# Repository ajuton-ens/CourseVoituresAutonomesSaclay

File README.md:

# Course de Voitures Autonomes Paris-Saclay CoVAPSy
Ce dépôt regroupe les documents et ressources liées à la course de voitures autonomes 1/10ème de Paris Saclay : https://ajuton-ens.github.io/CourseVoituresAutonomesSaclay/

Il est possible de s'inscrire ou d'obtenir plus d'informations en envoyant un mail à : anthony.juton@ens-paris-saclay.fr 

Le dossier _Simulator_ propose un simulateur Webots R2023b avec une voiture TT-02 équipée d'un lidar.
L'Efrei a aussi déposé un simulateur Webots.

Les cartes électroniques (pdf et fichiers Eagle) et les pièces mécaniques (fichiers step) de la voiture type sont dans le dossier _Hardware_.

---------------------------------------------
# Autonomous Car Race Paris-Saclay CoVAPSy

This repository contains documents and resources related to the 1/10th self-driving car race in Paris-Saclay: https://ajuton-ens.github.io/CourseVoituresAutonomesSaclay/

You can register or obtain more information by sending an email to: anthony.juton@ens-paris-saclay.fr

The folder _Simulator_ includes a Webots R2023b simulator with a TT-02 car equipped with a lidar.
Efrei has also submitted a Webots simulator.

The electronic boards (PDF and Eagle files) and mechanical parts (Step files) for the typical car are in the folder _Hardware_.

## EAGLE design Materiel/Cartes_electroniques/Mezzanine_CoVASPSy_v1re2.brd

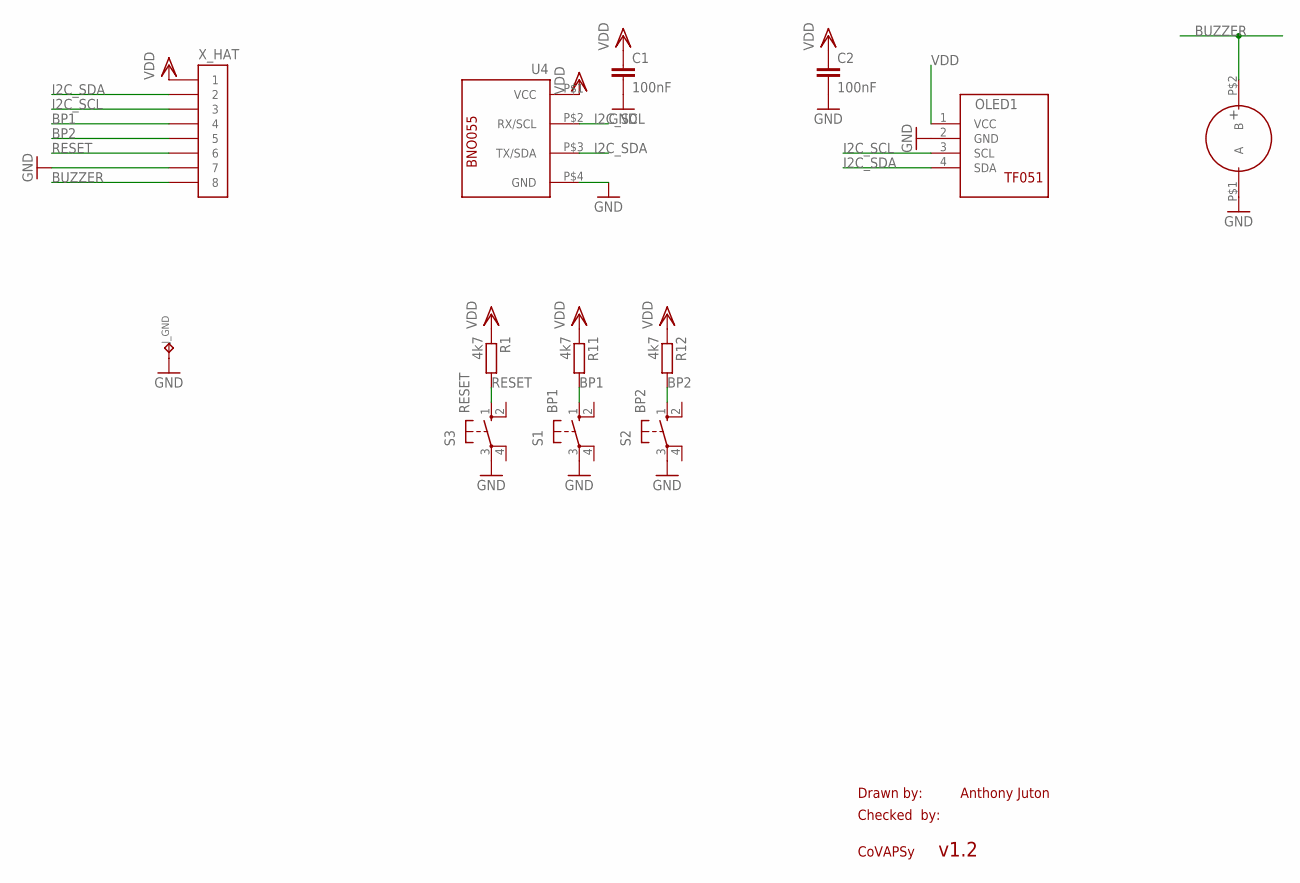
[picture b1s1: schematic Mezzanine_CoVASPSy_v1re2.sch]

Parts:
BUZZER: BUZZER_SMA13_P75; BUZZER_SMA_13_P75
C1, C2: 100nF; C1206K
J_GND: COSSE_POIGN; COSSE_POIGNARD
OLED1: ECRAN_OLED_TF051
R1, R11, R12: 4k7; M1206
S1: BP1; B3F-10XX
S2: BP2; B3F-10XX
S3: RESET; B3F-10XX
U4: MODULE_BNO055
X_HAT: MOLEX_8_COUDE

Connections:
BP1: R11.2, S1.1 (S), X_HAT.P$4 (4)
BP2: R12.2, S2.1 (S), X_HAT.P$5 (5)
BUZZER: BUZZER.P$2 (B), X_HAT.P$8 (8)
GND: BUZZER.P$1 (A), C1.2, C2.2, J_GND.P$1, OLED1.2 (GND), S1.3, S2.3, S3.3, U4.P$4 (GND), X_HAT.P$7 (7)
I2C_SCL: OLED1.3 (SCL), U4.P$2 (RX/SCL), X_HAT.P$3 (3)
I2C_SDA: OLED1.4 (SDA), U4.P$3 (TX/SDA), X_HAT.P$2 (2)
RESET: R1.2, S3.1 (S), X_HAT.P$6 (6)
VDD: C1.1, C2.1, OLED1.1 (VCC), R1.1, R11.1, R12.1, U4.P$1 (VCC), X_HAT.P$1 (1)

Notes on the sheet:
Drawn by:
Checked by:
CoVAPSy
Anthony Juton
v1.2

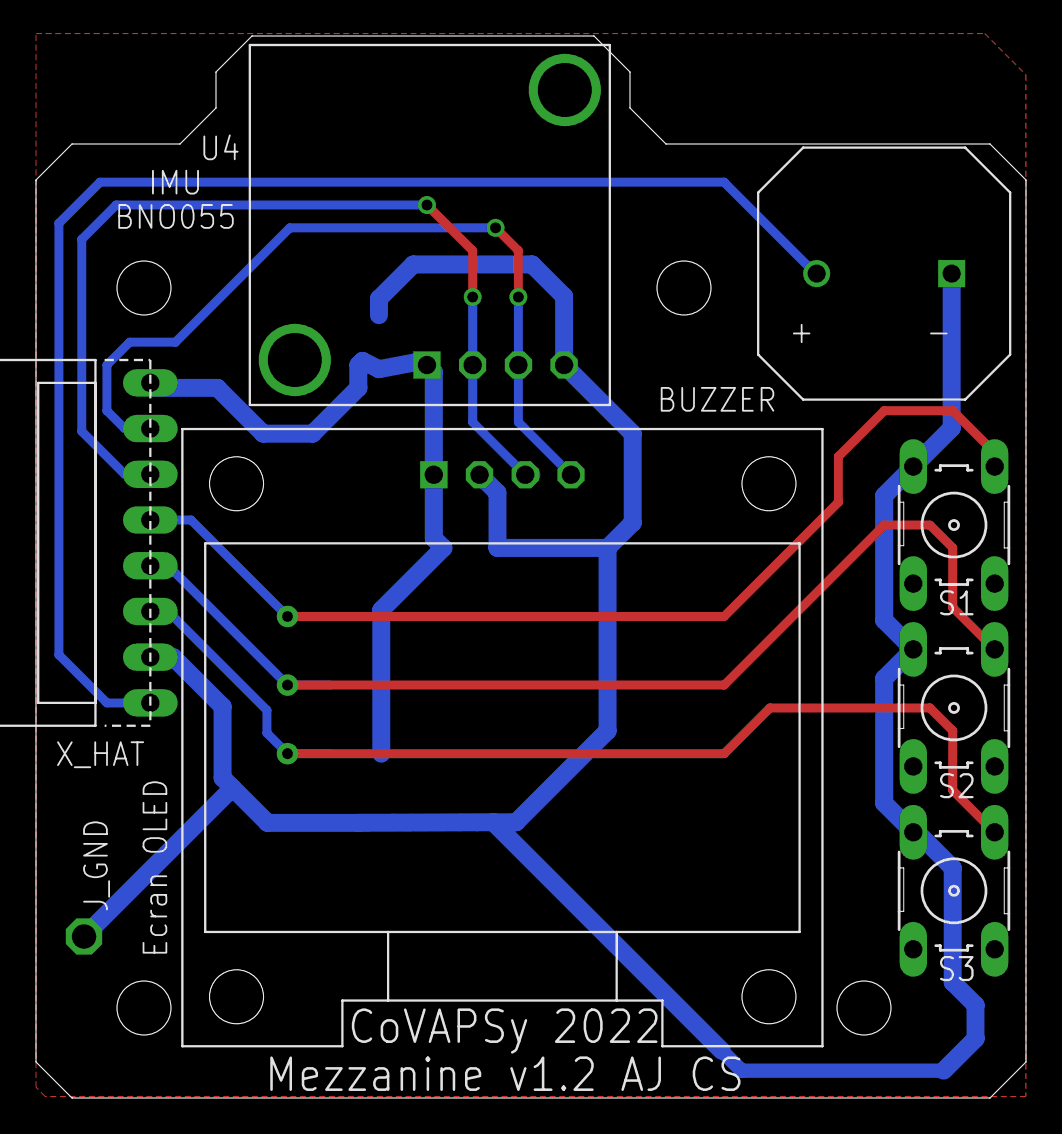
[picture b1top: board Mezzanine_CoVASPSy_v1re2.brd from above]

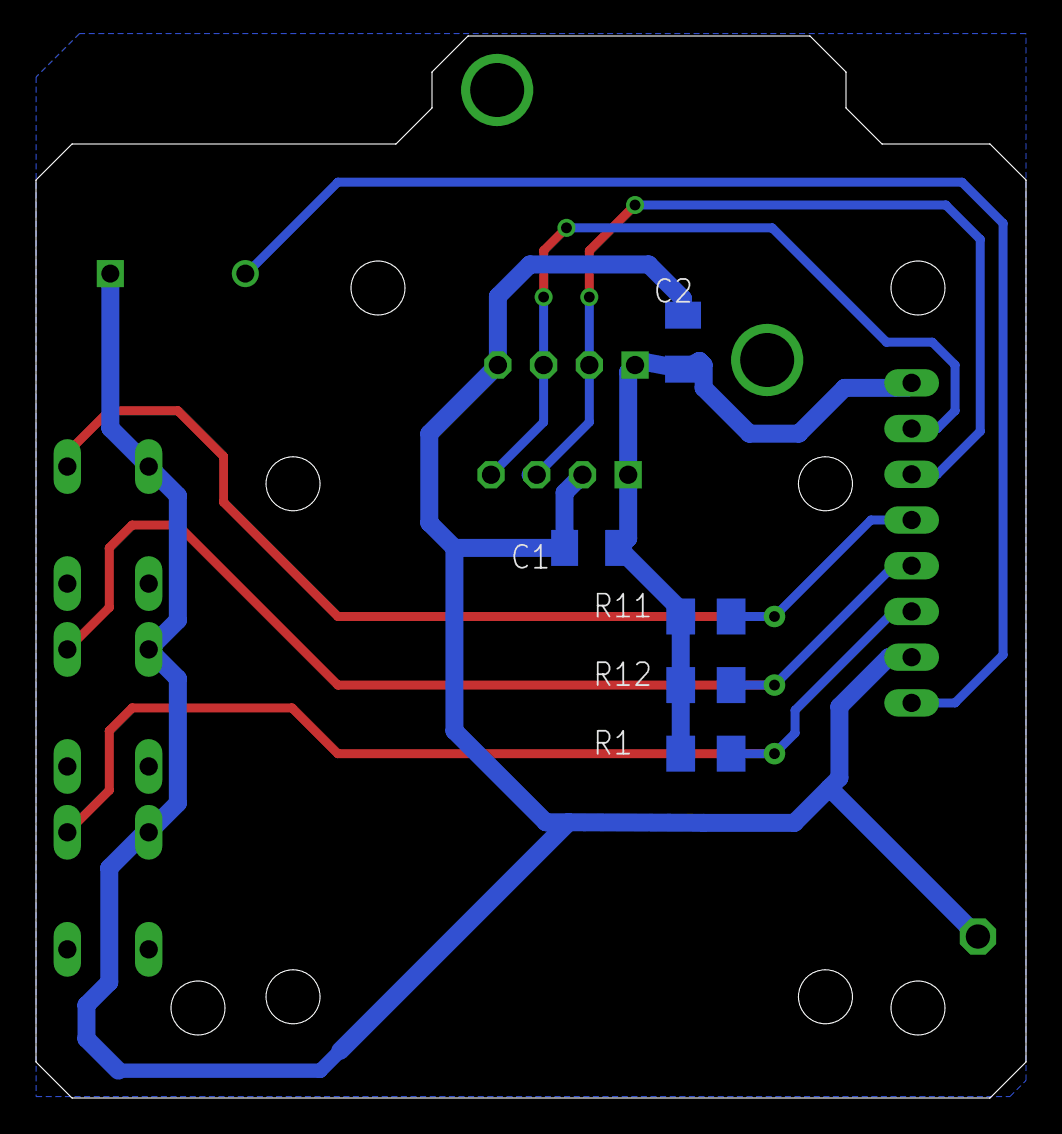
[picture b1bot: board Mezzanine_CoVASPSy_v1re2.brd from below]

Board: 2 copper layers, 55.0 x 59.0 mm, 13 parts (5 on the bottom side), 8 nets.

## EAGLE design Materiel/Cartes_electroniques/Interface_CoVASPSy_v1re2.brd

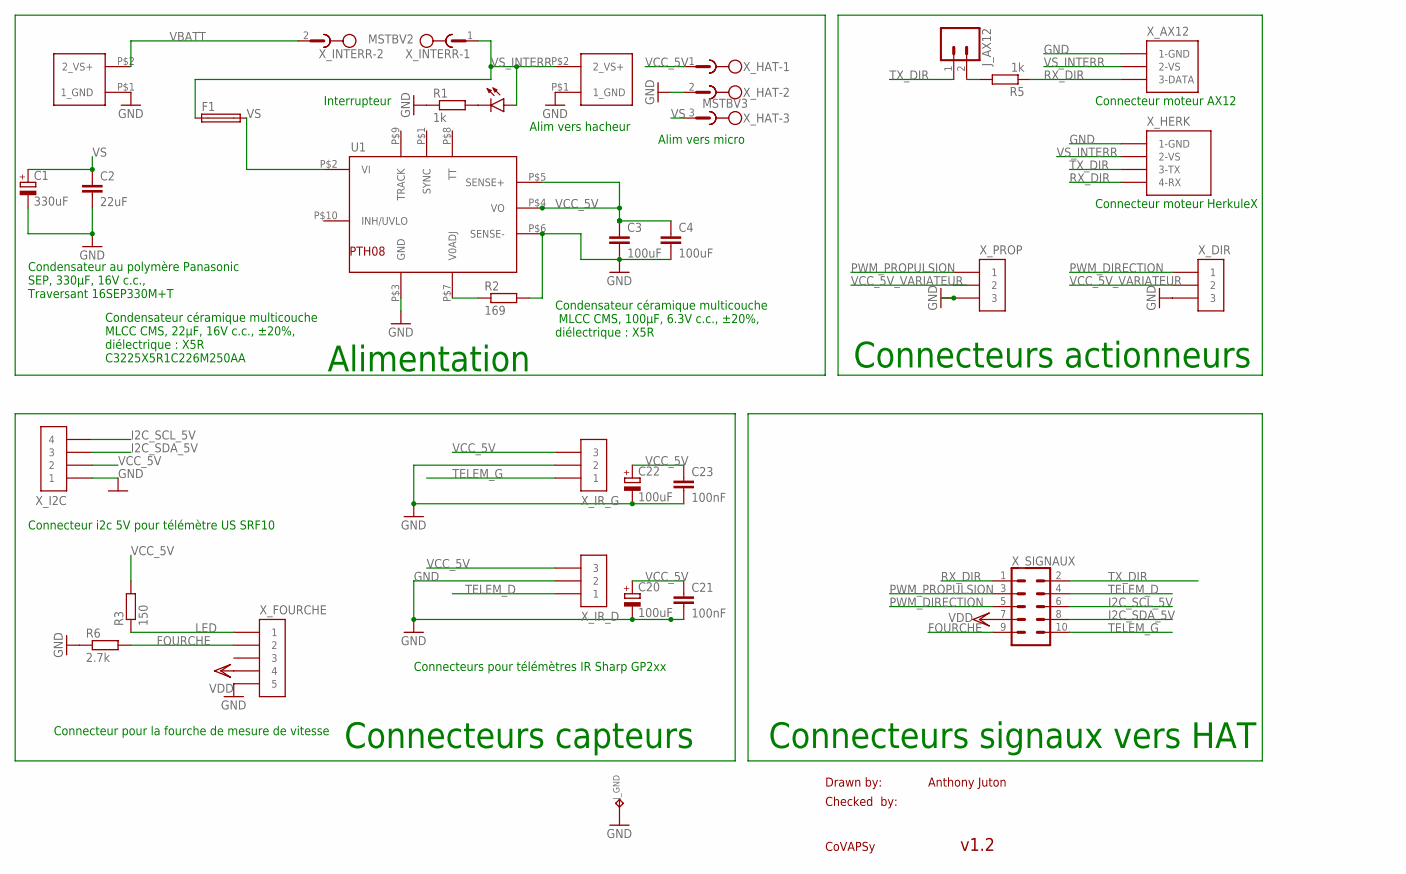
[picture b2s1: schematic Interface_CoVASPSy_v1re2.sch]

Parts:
C1: 330uF; E3,5-10
C2: 22uF; C1210
C3, C4: 100uF; C1206K
C20, C22: 100uF; A/3216-18W
C21, C23: 100nF; C1206
F1: SH22,5
J_AX12: CONN_02; 1X02
J_GND: COSSE_POIGN; COSSE_POIGNARD
LED1: LEDSML1206; SML1206
R1, R5: 1k; M1206
R2: 169; R0805
R3: 150; M1206
R6: 2.7k; M1206
U1: CONV_TI_PTH08; CONV_TI_PTH8
X_AX12: MOLEX_AX12
X_BATT: CONN_ALIM_TROU
X_DIR: CAVALIER_3
X_FOURCHE: MOLEX_5_DROIT
X_HACH: CONN_ALIM_TROU
X_HAT: MSTBV3
X_HERK: TE_HERKULEX
X_I2C: MOLEX_4_DROIT
X_INTERR: MSTBV2
X_IR_D: JST_3
X_IR_G: JST_3
X_PROP: CAVALIER_3
X_SIGNAUX: CONN_05X2SHD; 2X5-SHROUDED

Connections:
FOURCHE: R6.2, X_FOURCHE.P$2 (2), X_SIGNAUX.9
GND: C1.-, C2.2, C3.2, C4.2, C20.-, C21.2, C22.-, C23.2, J_GND.P$1, R1.1, R2.2, R6.1, U1.P$3 (GND), U1.P$6 (SENSE-), X_AX12.P$1 (1-GND), X_BATT.P$1 (1_GND), X_DIR.P$3 (3), X_FOURCHE.P$5 (5), X_HACH.P$1 (1_GND), X_HAT.2, X_HERK.P$1 (1-GND), X_I2C.P$1 (1), X_IR_D.P$2 (2), X_IR_G.P$2 (2), X_PROP.P$3 (3)
I2C_SCL_5V: X_I2C.P$4 (4), X_SIGNAUX.6
I2C_SDA_5V: X_I2C.P$3 (3), X_SIGNAUX.8
LED: R3.1, X_FOURCHE.P$1 (1)
unnamed: LED1.C, R1.2
unnamed: J_AX12.2, R5.2
unnamed: R2.1, U1.P$7 (V0ADJ)
PWM_DIRECTION: X_DIR.P$1 (1), X_SIGNAUX.5
PWM_PROPULSION: X_PROP.P$1 (1), X_SIGNAUX.3
RX_DIR: R5.1, X_AX12.P$3 (3-DATA), X_HERK.P$4 (4-RX), X_SIGNAUX.1
TELEM_D: X_IR_D.P$1 (1), X_SIGNAUX.4
TELEM_G: X_IR_G.P$1 (1), X_SIGNAUX.10
TX_DIR: J_AX12.1, X_HERK.P$3 (3-TX), X_SIGNAUX.2
VBATT: X_BATT.P$2 (2_VS+), X_INTERR.2
VCC_5V: C3.1, C4.1, C20.+, C21.1, C22.+, C23.1, R3.2, U1.P$4 (VO), U1.P$5 (SENSE+), X_HAT.1, X_I2C.P$2 (2), X_IR_D.P$3 (3), X_IR_G.P$3 (3)
VCC_5V_VARIATEUR: X_DIR.P$2 (2), X_PROP.P$2 (2)
VDD: X_FOURCHE.P$4 (4), X_SIGNAUX.7
VS: C1.+, C2.1, F1.2, U1.P$2 (VI), X_HAT.3
VS_INTERR: F1.1, LED1.A, X_AX12.P$2 (2-VS), X_HACH.P$2 (2_VS+), X_HERK.P$2 (2-VS), X_INTERR.1

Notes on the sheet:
Drawn by:
Checked by:
CoVAPSy
Anthony Juton
v1.2
Connecteur moteur AX12
Connecteur pour la fourche de mesure de vitesse
Connecteur moteur HerkuleX
Connecteurs actionneurs
Condensateur au polymère Panasonic SEP, 330μF, 16V c.c., Traversant 16SEP330M+T
Condensateur céramique multicouche MLCC CMS, 22μF, 16V c.c., ±20%, diélectrique : X5R C3225X5R1C226M250AA
Condensateur céramique multicouche MLCC CMS, 100μF, 6.3V c.c., ±20%, diélectrique : X5R
Alimentation
Alim vers hacheur
Interrupteur
Alim vers micro
Connecteurs capteurs
Connecteur i2c 5V pour télémètre US SRF10
Connecteurs pour télémètres IR Sharp GP2xx
Connecteurs signaux vers HAT

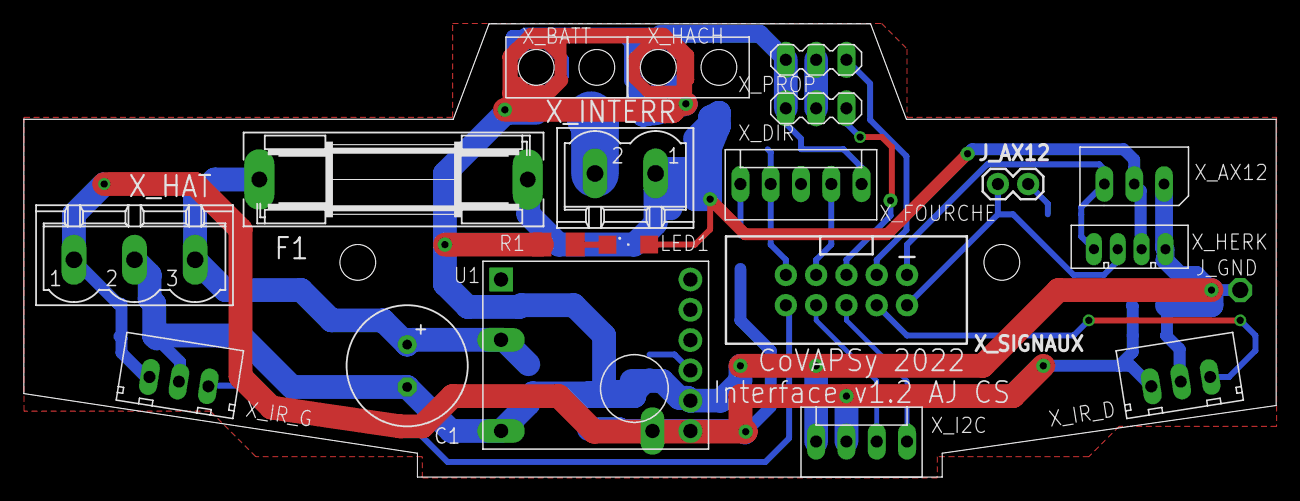
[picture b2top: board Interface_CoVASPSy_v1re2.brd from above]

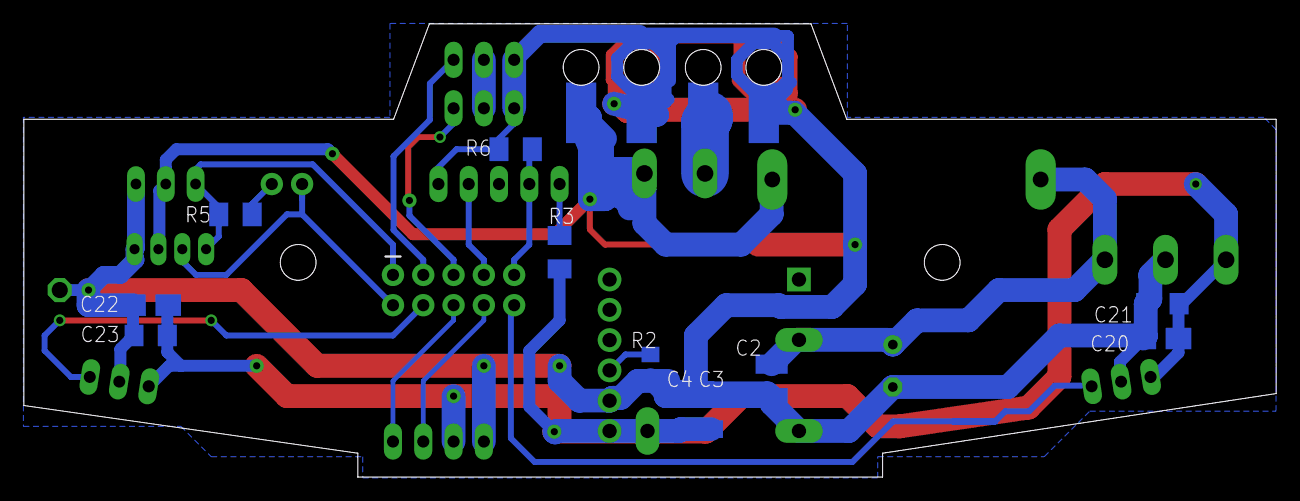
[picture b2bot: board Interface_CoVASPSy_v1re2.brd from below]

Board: 2 copper layers, 105.0 x 38.0 mm, 31 parts (11 on the bottom side), 20 nets.

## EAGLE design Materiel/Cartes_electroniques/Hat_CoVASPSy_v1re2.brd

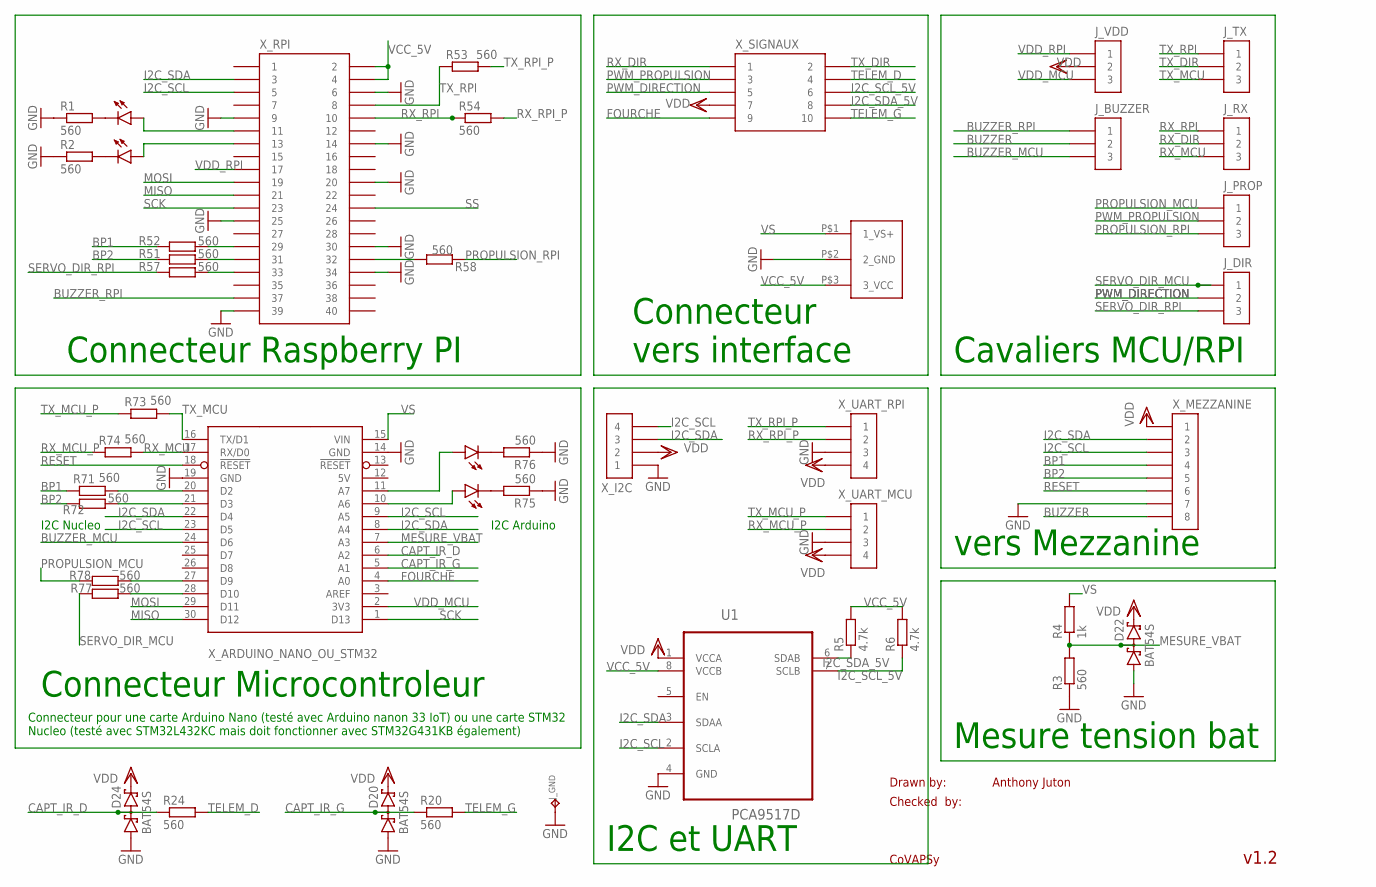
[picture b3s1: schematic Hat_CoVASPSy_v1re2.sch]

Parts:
D20, D22, D24: BAT54S; SOT23
J_BUZZER: CAVALIER_3
J_DIR: CAVALIER_3
J_GND: COSSE_POIGN; COSSE_POIGNARD
J_PROP: CAVALIER_3
J_RX: CAVALIER_3
J_TX: CAVALIER_3
J_VDD: CAVALIER_3
LED1, LED2, LED3, LED4: LEDSML1206; SML1206
R1, R2, R3, R20, R24, R51, R52, R53, R54, R57, R58, R71, R72, R73, R74, R75, R76, R77, R78: 560; M1206
R4: 1k; M1206
R5, R6: 4.7k; M1206
U1: PCA9517D; SOIC127P600X175-8N
X_ALIM: CONN_ALIM_3TROUS
X_ARDUINO_NANO_OU_STM32: ARDUINO_NANO_STM32_NUCLEO
X_I2C: MOLEX_4_DROIT
X_MEZZANINE: MOLEX_8_DROIT
X_RPI: HEADER_20X2
X_SIGNAUX: HEADER_5X2
X_UART_MCU: MOLEX_4_DROIT
X_UART_RPI: MOLEX_4_DROIT

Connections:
5V: X_ARDUINO_NANO_OU_STM32.12 (5V)
BP1: R52.1, R71.1, X_MEZZANINE.P$4 (4)
BP2: R51.1, R72.1, X_MEZZANINE.P$5 (5)
BUZZER: J_BUZZER.P$2 (2), X_MEZZANINE.P$8 (8)
BUZZER_MCU: J_BUZZER.P$3 (3), X_ARDUINO_NANO_OU_STM32.24 (D6)
BUZZER_RPI: J_BUZZER.P$1 (1), X_RPI.P$37 (37)
CAPT_IR_D: D24.3 (C1A2), R24.1, X_ARDUINO_NANO_OU_STM32.6 (A2)
CAPT_IR_G: D20.3 (C1A2), R20.1, X_ARDUINO_NANO_OU_STM32.5 (A1)
FOURCHE: X_ARDUINO_NANO_OU_STM32.4 (A0), X_SIGNAUX.P$9 (9)
GND: D20.1 (A1), D22.1 (A1), D24.1 (A1), J_GND.P$1, R1.1, R2.1, R3.1, R75.1, R76.1, U1.4 (GND), X_ALIM.P$2 (2_GND), X_ARDUINO_NANO_OU_STM32.14 (GND), X_ARDUINO_NANO_OU_STM32.19 (GND), X_I2C.P$1 (1), X_MEZZANINE.P$7 (7), X_RPI.P$6 (6), X_RPI.P$9 (9), X_RPI.P$14 (14), X_RPI.P$20 (20), X_RPI.P$25 (25), X_RPI.P$30 (30), X_RPI.P$34 (34), X_RPI.P$39 (39), X_UART_MCU.P$3 (3), X_UART_RPI.P$3 (3)
I2C_SCL: U1.2 (SCLA), X_ARDUINO_NANO_OU_STM32.9 (A5), X_ARDUINO_NANO_OU_STM32.23 (D5), X_I2C.P$4 (4), X_MEZZANINE.P$3 (3), X_RPI.P$5 (5)
I2C_SCL_5V: R6.1, U1.7 (SCLB), X_SIGNAUX.P$6 (6)
I2C_SDA: U1.3 (SDAA), X_ARDUINO_NANO_OU_STM32.8 (A4), X_ARDUINO_NANO_OU_STM32.22 (D4), X_I2C.P$3 (3), X_MEZZANINE.P$2 (2), X_RPI.P$3 (3)
I2C_SDA_5V: R5.1, U1.6 (SDAB), X_SIGNAUX.P$8 (8)
MESURE_VBAT: D22.3 (C1A2), R3.2, R4.1, X_ARDUINO_NANO_OU_STM32.7 (A3)
MISO: X_ARDUINO_NANO_OU_STM32.30 (D12), X_RPI.P$21 (21)
MOSI: X_ARDUINO_NANO_OU_STM32.29 (D11), X_RPI.P$19 (19)
unnamed: LED1.C, R1.2
unnamed: LED3.A, X_ARDUINO_NANO_OU_STM32.11 (A7)
unnamed: R71.2, X_ARDUINO_NANO_OU_STM32.20 (D2)
unnamed: R72.2, X_ARDUINO_NANO_OU_STM32.21 (D3)
unnamed: LED2.C, R2.2
unnamed: LED1.A, X_RPI.P$11 (11)
unnamed: R52.2, X_RPI.P$29 (29)
unnamed: R77.2, X_ARDUINO_NANO_OU_STM32.28 (D10)
unnamed: R51.2, X_RPI.P$31 (31)
unnamed: LED3.C, R76.2
unnamed: LED2.A, X_RPI.P$13 (13)
unnamed: R57.2, X_RPI.P$33 (33)
unnamed: R58.1, X_RPI.P$32 (32)
unnamed: R78.2, X_ARDUINO_NANO_OU_STM32.27 (D9)
unnamed: LED4.A, X_ARDUINO_NANO_OU_STM32.10 (A6)
unnamed: LED4.C, R75.2
PROPULSION_MCU: J_PROP.P$1 (1), R78.1
PROPULSION_RPI: J_PROP.P$3 (3), R58.2
PWM_DIRECTION: J_DIR.P$2 (2), X_SIGNAUX.P$5 (5)
PWM_PROPULSION: J_PROP.P$2 (2), X_SIGNAUX.P$3 (3)
RESET: X_ARDUINO_NANO_OU_STM32.18 (!RESET), X_MEZZANINE.P$6 (6)
RX_DIR: J_RX.P$2 (2), X_SIGNAUX.P$1 (1)
RX_MCU: J_RX.P$3 (3), R74.2, X_ARDUINO_NANO_OU_STM32.17 (RX/D0)
RX_MCU_P: R74.1, X_UART_MCU.P$2 (2)
RX_RPI: J_RX.P$1 (1), R54.1, X_RPI.P$10 (10)
RX_RPI_P: R54.2, X_UART_RPI.P$2 (2)
SCK: X_ARDUINO_NANO_OU_STM32.1 (D13), X_RPI.P$23 (23)
SERVO_DIR_MCU: J_DIR.P$1 (1), R77.1
SERVO_DIR_RPI: J_DIR.P$3 (3), R57.1
SS: X_RPI.P$24 (24)
TELEM_D: R24.2, X_SIGNAUX.P$4 (4)
TELEM_G: R20.2, X_SIGNAUX.P$10 (10)
TX_DIR: J_TX.P$2 (2), X_SIGNAUX.P$2 (2)
TX_MCU: J_TX.P$3 (3), R73.2, X_ARDUINO_NANO_OU_STM32.16 (TX/D1)
TX_MCU_P: R73.1, X_UART_MCU.P$1 (1)
TX_RPI: J_TX.P$1 (1), R53.1, X_RPI.P$8 (8)
TX_RPI_P: R53.2, X_UART_RPI.P$1 (1)
VCC_5V: R5.2, R6.2, U1.8 (VCCB), X_ALIM.P$3 (3_VCC), X_RPI.P$2 (2), X_RPI.P$4 (4)
VDD: D20.2 (C2), D22.2 (C2), D24.2 (C2), J_VDD.P$2 (2), U1.1 (VCCA), X_I2C.P$2 (2), X_MEZZANINE.P$1 (1), X_SIGNAUX.P$7 (7), X_UART_MCU.P$4 (4), X_UART_RPI.P$4 (4)
VDD_MCU: J_VDD.P$3 (3), X_ARDUINO_NANO_OU_STM32.2 (3V3)
VDD_RPI: J_VDD.P$1 (1), X_RPI.P$17 (17)
VS: R4.2, X_ALIM.P$1 (1_VS+), X_ARDUINO_NANO_OU_STM32.15 (VIN)

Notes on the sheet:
Drawn by:
Checked by:
CoVAPSy
Anthony Juton
v1.2
I2C Arduino
I2C Nucleo
Cavaliers MCU/RPI
Connecteur pour une carte Arduino Nano (testé avec Arduino nanon 33 IoT) ou une carte STM32 Nucleo (testé avec STM32L432KC mais doit fonctionner avec STM32G431KB également)
Connecteur Raspberry PI
Connecteur vers interface
Connecteur Microcontroleur
vers Mezzanine
Mesure tension bat
I2C et UART

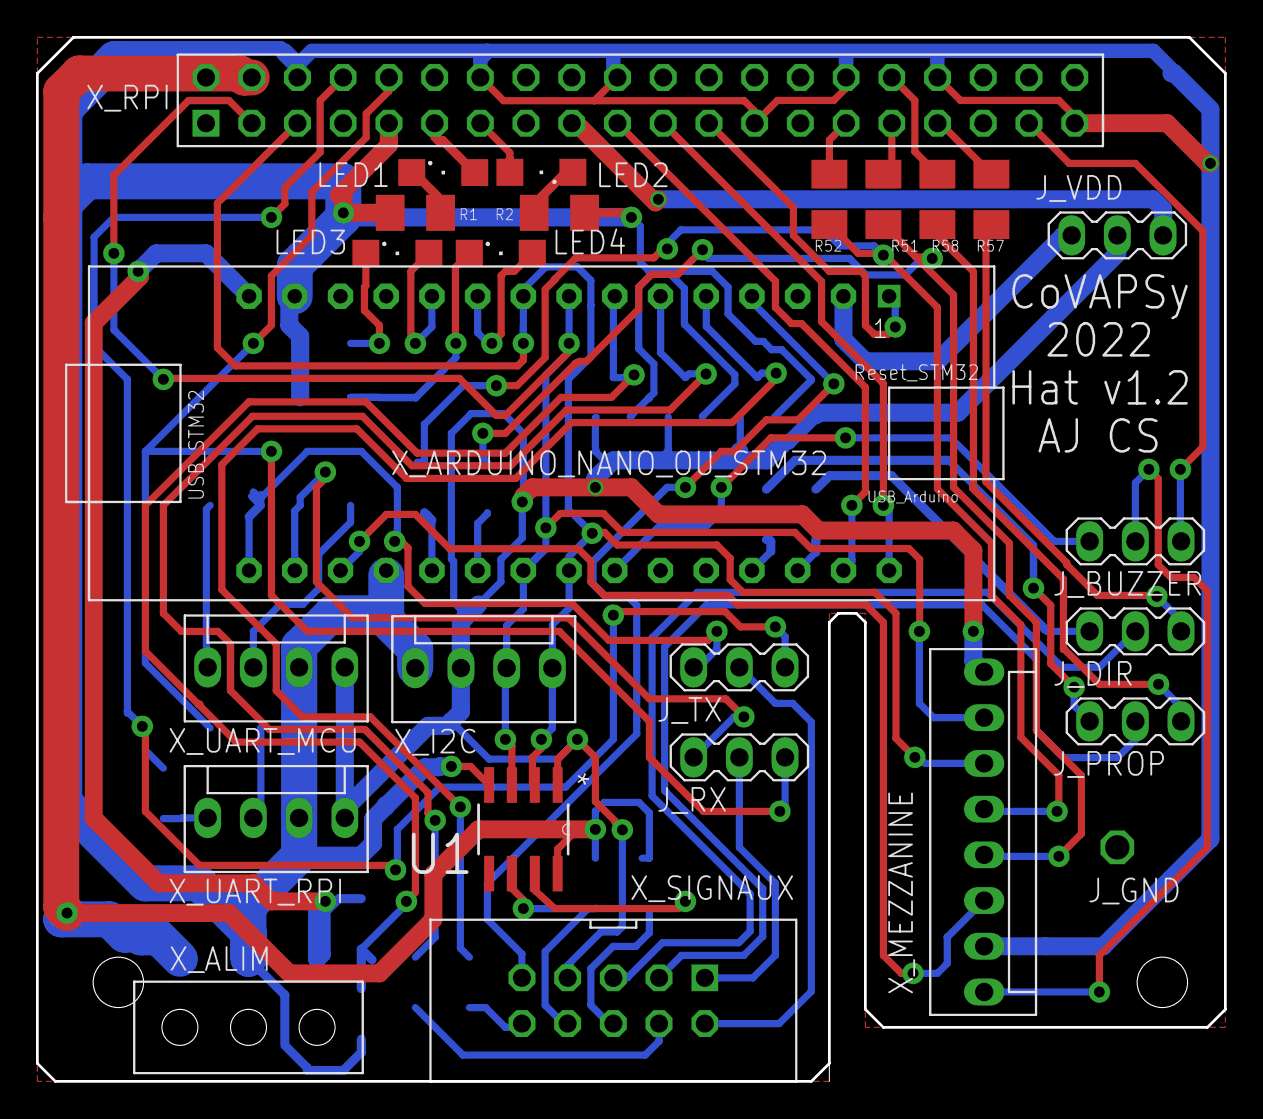
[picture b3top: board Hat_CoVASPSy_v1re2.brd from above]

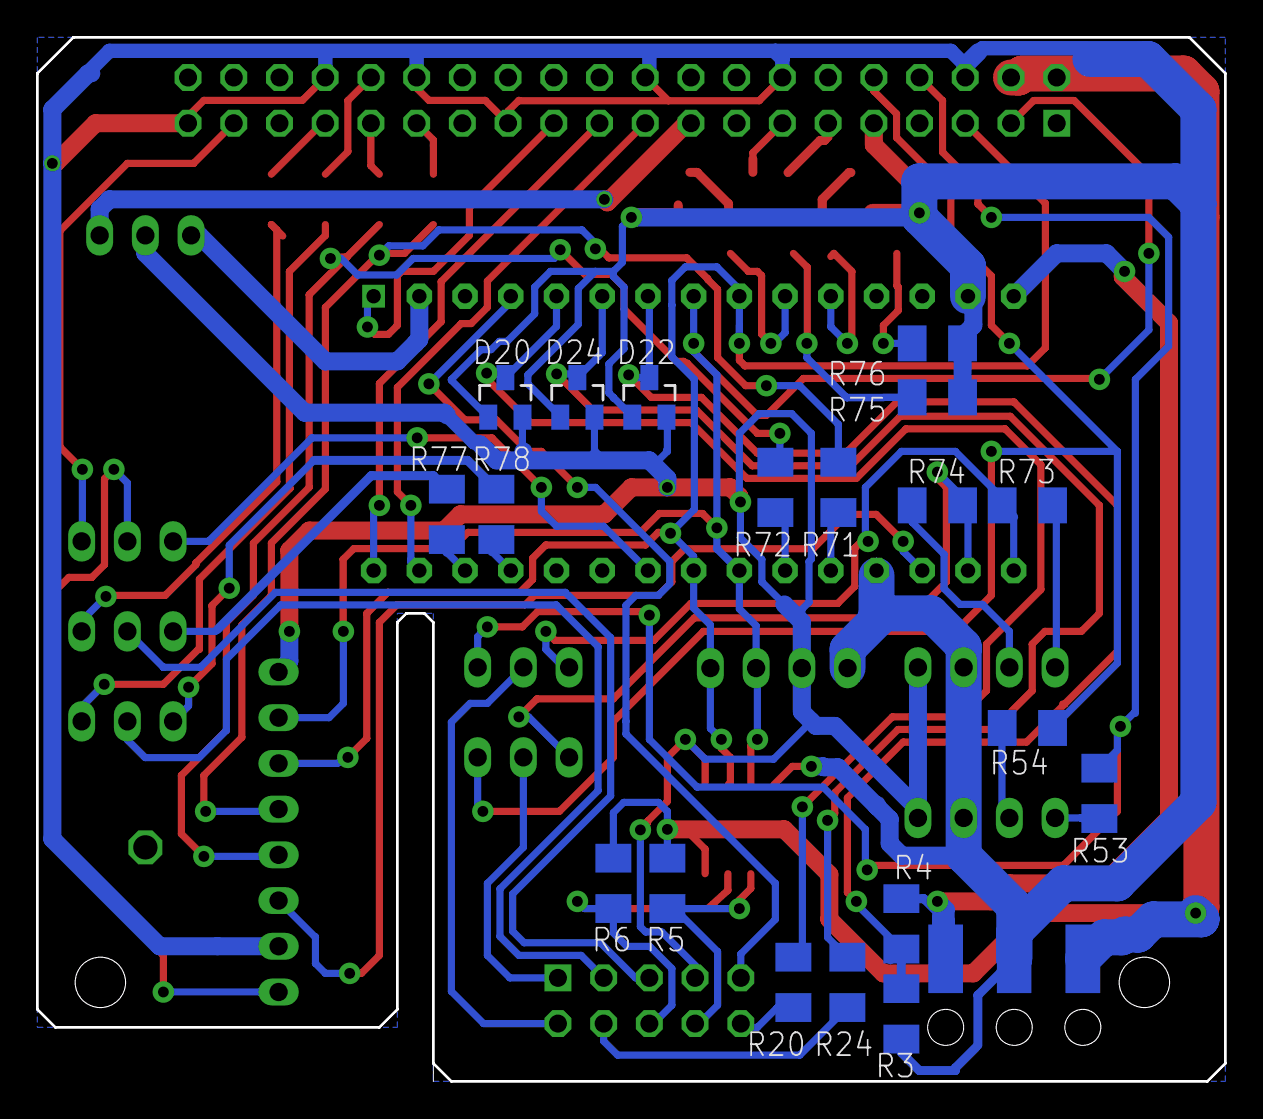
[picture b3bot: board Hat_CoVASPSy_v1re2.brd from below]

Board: 2 copper layers, 66.0 x 58.0 mm, 45 parts (19 on the bottom side), 57 nets.

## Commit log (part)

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2021-06-22 ajout videos
2021-06-22 ajout images
2021-06-22 ajout des videos
2021-06-22 ajout du réglement
2021-06-22 ajout du reglement
2021-06-22 ajout de matériel et Photos
2021-06-22 ajout de docs
2021-06-22 Set theme jekyll-theme-cayman
2021-06-22 Ajout de l'image de la voiture de Gauthier
2021-06-22 Ajout du site Mkdocs
2021-06-22 Deployed 5d276be with MkDocs version: 1.1.2
2021-06-23 MAJ image dimmensions voiture
2021-06-23 Deployed 3d16d1c with MkDocs version: 1.1.2
2022-08-25 ajout des CR de réunion
2022-08-25 Deployed 229a898 with MkDocs version: 1.3.1
2022-08-25 Create test
2022-08-25 MAJ du site
2022-08-25 Deployed 96f5b05 with MkDocs version: 1.3.1
2022-08-26 MAJ du site web
2022-08-26 Deployed da456c1 with MkDocs version: 1.3.1
2022-08-26 Ajout de photos et videos
2022-08-26 ajout des photos
2022-08-26 ajout photos
2022-08-26 ajout des vidéos
2022-08-26 Deployed 5f11fe4 with MkDocs version: 1.3.1
2022-08-29 ajout d'éléments dans Matériel et des CR de réunion dans docs
2022-08-29 ajout des images 3D de la voiture dans Materiel
2022-08-31 MAJ nom logo
2022-08-31 ajout d'éléments pour le simulateur webots
2022-10-28 ajout de l'exemple d'apprentissage par renforcement sous webots avec Altino
2022-10-28 ajout des images DALL-E
2022-10-28 ajout de quelques photos
2022-11-17 Ajout des modèles 3D des bords de piste
2022-11-25 Ajout des cartes électroniques (Schéma, PCB, PDF)
2022-12-14 ajout du bloc 0.5m
2022-12-15 ajout de la piste 2022
2023-01-11 ajout des programmes de test arduino
2023-01-19 Webots world and driving logic Efrei
2023-01-20 Add files via upload
    Ajout des guides pour le montage des cartes électroniques
2023-01-25 ajout du simulateur ENS Webots R2022b avec TT02 et éléments de piste
2023-01-25 ajout du simulateur CoVAPSy Webots R2022b
2023-01-25 Ajout des photos de la voiture type version janvier 2023
2023-01-25 mise à jour de la page web
2023-01-25 Deployed 80ce44c with MkDocs version: 1.3.1
2023-01-26 remise en ligne des éléments de piste
2023-01-26 Modification de la photo de la voiture avec carrosserie
2023-01-26 Add files via upload
    Mise à jour de la vue 3D avec carrosserie
2023-01-27 Ajout CAO
2023-01-27 Create CAO
2023-02-01 Mise à jour des références matérielles, mise en ordre du dossier matériel
2023-02-01 Mise en ordre du dossier Pièces matérielles
2023-02-01 Deployed daf7ceb with MkDocs version: 1.3.1
2023-02-01 Ajout d'un simulateur avec les élements pour construire une piste personnalisée et avec 2 voitures
2023-02-01 Deployed 162f45c with MkDocs version: 1.3.1
2023-02-07 ajout du fichier cavalier connecteurs
2023-02-08 Ajoute des fiches de mises en oeuvre STM32
2023-02-08 MAJ de la fiche SPI
2023-02-17 Ajout CR réunion du 16/02/2023
2023-02-22 Rename 011.1-Plaque trouée.dxf to Plaque trouée.dxf
2023-02-22 Rename 011.2-Plaque trouée supérieure.dxf to Plaque trouée supérieure.dxf
2023-03-06 mise à jour doc SPI STM32
2023-03-13 Fichier de découpe pignon intermédiaire
2023-04-13 Ajout des présentations des voitures
2023-04-15 ajout dernières présentations
2023-08-23 ajout du projet de base Webots 2023b
2023-08-24 MAJ Simulateur
2023-08-24 ajout des programmes python de base
2023-08-24 retrait de numpy du contrôleur de base pour webots
2023-09-05 Deployed 15f38e1 with MkDocs version: 1.3.1
2023-09-13 Mise à jour vers 2023b
2023-10-04 MAJ des prog python de base
2023-10-04 ajout prog PS4
2023-10-04 ajout du dossier pour les fichiers c
2023-10-09 MAJ du simulateur
2023-11-19 Deployed 23b9d73 with MkDocs version: 1.3.1
2023-12-11 Deployed 847a7ab with MkDocs version: 1.3.1
2023-12-13 ajout des bibliothèques C
2023-12-21 ajout du projet L432
2024-01-13 modif des bibliotheques python
2024-01-17 MAJ des pièces du kit et guide d'assemblage
2024-01-18 Create Programmes_Demo_STM32
2024-01-18 Ajout du programme capteurs/écran pour la STM32
2024-01-28 Create Voiture STM32
2024-03-07 Deployed 2f4a01c with MkDocs version: 1.3.1
2024-03-07 Deployed 19aa490 with MkDocs version: 1.3.1
2024-03-07 MAJ du tutoriel installation de la RPI
2024-03-29 ajout du programme pour homologuer la détection des voitures
2024-09-09 Deployed fa5ee20 with MkDocs version: 1.3.1
2024-10-17 MAJ du fichier Installation rapsberry pi
2025-02-02 Deployed d17d7c5 with MkDocs version: 1.3.1
2025-03-17 Deployed b812144 with MkDocs version: 1.3.1
2025-03-25 Deployed da4fcc9 with MkDocs version: 1.3.1
2025-06-25 MAJ de la page web
2025-09-15 Un peu de rangement
2025-09-15 MAJ site web
2025-09-15 Deployed d281cab with MkDocs version: 1.6.1
2025-09-15 MAJ site, traduction en anglais
2025-09-15 Deployed b77d77e with MkDocs version: 1.6.1
2025-10-13 MAJ du fichier simulateur 2025a
2025-10-16 Deployed 099d7bf with MkDocs version: 1.6.1
2026-01-14 Ajout du programme de lecture de la vitesse de la voiture
2026-01-21 MAJ du fichier simulateur
2026-01-26 Deployed 079841a with MkDocs version: 1.6.1

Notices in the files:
parts and their libraries:
SparkFun-Connectors: Licensing: Creative Commons ShareAlike 4.0 International - https://creativecommons.org/licenses/by-sa/4.0
